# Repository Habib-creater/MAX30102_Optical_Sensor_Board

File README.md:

# MAX30102 Optical Sensor Board

<p align="center">
  <strong>MAX30102 • Dual Supply Rails • I²C • 2-Layer PCB • KiCad</strong>
</p>

<p align="center">
  A compact optical sensing board centered on the MAX30102
  integrated pulse-oximetry and heart-rate sensor.
</p>

<p align="center">
  <a href="docs/max30102_schematic.pdf">Schematic</a> •
  <a href="bom/MAX30102_BOM.csv">BOM</a> •
  <a href="manufacturing/gerbers/">Gerbers</a> •
  <a href="hardware/kicad/">KiCad Files</a>
</p>

---

## Overview

The **MAX30102 Optical Sensor Board** is a compact 2-layer PCB designed
around the **MAX30102** sensor.

The board provides the MAX30102 with dedicated supply regulation,
I²C connectivity, interrupt access, and a 5-pin external interface.

The complete hardware design package is included in this repository,
covering the native **KiCad project**, schematic, PCB layout, BOM,
Gerber and drill manufacturing files, pick-and-place data, and board
documentation.

---

## Quick Access

| Resource | Description |
|---|---|
| 📐 [Schematic PDF](docs/max30102_schematic.pdf) | Electrical schematic |
| 📦 [Bill of Materials](bom/MAX30102_BOM.csv) | Component BOM |
| 🏭 [Gerber & Drill Files](manufacturing/gerbers/) | PCB manufacturing data |
| 🔧 [KiCad Project](hardware/kicad/) | Native KiCad design files |
| 🖼️ [Board Images](docs/images/) | 3D renders and PCB views |
| 📍 [Pick-and-Place Data](manufacturing/pick-and-place/) | Component placement files |

---

## Key Features

| Feature | Details |
|---|---|
| **Optical Sensor** | MAX30102 |
| **Sensor Function** | Pulse oximetry and heart-rate sensing |
| **Digital Interface** | I²C |
| **Interrupt** | Dedicated INT connection |
| **Input Supply** | +5 V |
| **Logic / Sensor Rail** | +3.3 V |
| **LED Supply Rail** | +1.8 V |
| **3.3 V Regulator** | AP2112K-3.3 |
| **1.8 V Regulator** | TLV70018 |
| **Protection** | SMAJ5.0A TVS diode |
| **External Interface** | 1×5 pin header |
| **PCB** | 2-layer |
| **EDA Software** | KiCad |
| **PCB Thickness** | 1.6 mm |
| **Manufacturing Data** | Gerber + PTH/NPTH drill |
| **Assembly Data** | Pick-and-place CSV |

---

## PCB Preview

### 3D Board Render

### PCB Front Layout

### PCB Back Layout

### 3D Bottom View

---

## Hardware Architecture

The board is organized around the MAX30102 sensor and its associated
power and interface circuitry.

### MAX30102 Sensor

The **MAX30102** integrates optical sensing functionality for
pulse-oximetry and heart-rate applications.

The sensor interface exposes:

- I²C clock — SCL
- I²C data — SDA
- Interrupt — INT
- Sensor supply — +1.8 V
- LED supply — +3.3V V

### Power Architecture

The board contains dedicated regulation stages for the sensor system:

- **+5 V input**
- **AP2112K-3.3** for the +3.3 V rail
- **TLV70018** for the +1.8 V rail
- Input transient protection

### External Interface

A 5-pin header provides the primary external connection to the board.

| Pin | Signal |
|---|---|
| 1 | +3.3 V |
| 2 | GND |
| 3 | +5 V |
| 4 | SCL |
| 5 | SDA |

The interrupt signal is routed to the MAX30102 interface circuitry.

---

## PCB Design

The board is implemented as a **2-layer PCB** using **KiCad**.

### PCB Characteristics

- 2-layer signal routing
- 1.6 mm board thickness
- Compact sensor-oriented layout
- Dedicated regulated supply rails
- I²C interface routing
- MAX30102 sensor placement
- Input transient protection
- External 5-pin interface

---

## Design Files

The native KiCad project is located in:

[**hardware/kicad/**](hardware/kicad/)

### Main Files

| File | Description |
|---|---|
| `max30102_pcb.kicad_pro` | KiCad project |
| `max30102_pcb.kicad_sch` | Schematic source |
| `max30102_pcb.kicad_pcb` | PCB layout |

The exported schematic PDF is available in
[**docs/**](docs/).

---

## Manufacturing Outputs

The manufacturing package is available in:

[**manufacturing/gerbers/**](manufacturing/gerbers/)

The package contains:

- Front copper
- Back copper
- Front solder paste
- Back solder paste
- Front silkscreen
- Back silkscreen
- Front solder mask
- Back solder mask
- Board outline
- PTH drill data
- NPTH drill data
- Gerber job file

---

## Bill of Materials

The component BOM is available in:

[**bom/MAX30102_BOM.csv**](bom/MAX30102_BOM.csv)

The BOM contains the component references, quantities, values,
footprints, and available manufacturer/supplier information associated
with the design.

---

## Pick-and-Place Data

Assembly placement data is available in:

[**manufacturing/pick-and-place/**](manufacturing/pick-and-place/)

The package contains separate top-side and bottom-side component
position CSV files.

---

## Documentation

The repository includes:

- Electrical schematic PDF
- PCB front layout
- PCB back layout
- 3D top render
- 3D bottom render
- Bill of materials
- Manufacturing outputs
- Pick-and-place data
- Native KiCad design files

---

## Project Status

| Item | Status |
|---|---|
| Schematic | ✅ Completed |
| PCB Layout | ✅ Completed |
| PCB Layer Count | ✅ 2-layer |
| KiCad Project | ✅ Included |
| BOM | ✅ Included |
| Gerber Files | ✅ Generated |
| Drill Files | ✅ Generated |
| Pick-and-Place Data | ✅ Included |
| Documentation | ✅ Included |

---

## Repository Structure

```text
.
├── hardware/
│   └── kicad/
│       ├── max30102_pcb.kicad_pro
│       ├── max30102_pcb.kicad_sch
│       └── max30102_pcb.kicad_pcb
│
├── manufacturing/
│   ├── gerbers/
│   │   ├── max30102_pcb-F_Cu.gbr
│   │   ├── max30102_pcb-B_Cu.gbr
│   │   ├── max30102_pcb-F_Silkscreen.gbr
│   │   ├── max30102_pcb-B_Silkscreen.gbr
│   │   ├── max30102_pcb-F_Mask.gbr
│   │   ├── max30102_pcb-B_Mask.gbr
│   │   ├── max30102_pcb-F_Paste.gbr
│   │   ├── max30102_pcb-B_Paste.gbr
│   │   ├── max30102_pcb-Edge_Cuts.gbr
│   │   ├── max30102_pcb-PTH.drl
│   │   ├── max30102_pcb-NPTH.drl
│   │   └── max30102_pcb-job.gbrjob
│   │
│   └── pick-and-place/
│       ├── max30102_pcb-top-pos.csv
│       └── max30102_pcb-bottom-pos.csv
│
├── bom/
│   └── MAX30102_BOM.csv
│
├── docs/
│   ├── images/
│   │   ├── 3D_TOP.png
│   │   ├── 3D_BOTTOM.png
│   │   ├── Layout_front.png
│   │   └── Layout_back.png
│   │
│   └── max30102_schematic.pdf
│
├── .gitignore
├── CONTRIBUTING.md
├── LICENSE
└── README.md
```

---

## License

The hardware design files in this repository are licensed under the
**CERN Open Hardware Licence Version 2 - Strongly Reciprocal
(CERN-OHL-S-2.0)**.

The licence permits use, modification, distribution, and manufacture
under the terms of the CERN-OHL-S-2.0 licence, with the corresponding
source-sharing requirements for covered hardware.

**Copyright © 2026 Habib Ur Rehman**

See [`LICENSE`](LICENSE) for the licence identifier and official
licence reference.

---

## Author

### Habib Ur Rehman

**Electronics Engineering**  
**University of Engineering and Technology Peshawar (Abbottabad Campus)**

### Connect

- **GitHub:** [Habib-creater](https://github.com/Habib-creater)
- **LinkedIn:** [Habib Ur Rehman](https://www.linkedin.com/in/habib-ur-rehman-8321182b4/)

---

<p align="center">
  <strong>MAX30102 Optical Sensor Board</strong><br>
  Compact Open Hardware Sensor Platform
</p>

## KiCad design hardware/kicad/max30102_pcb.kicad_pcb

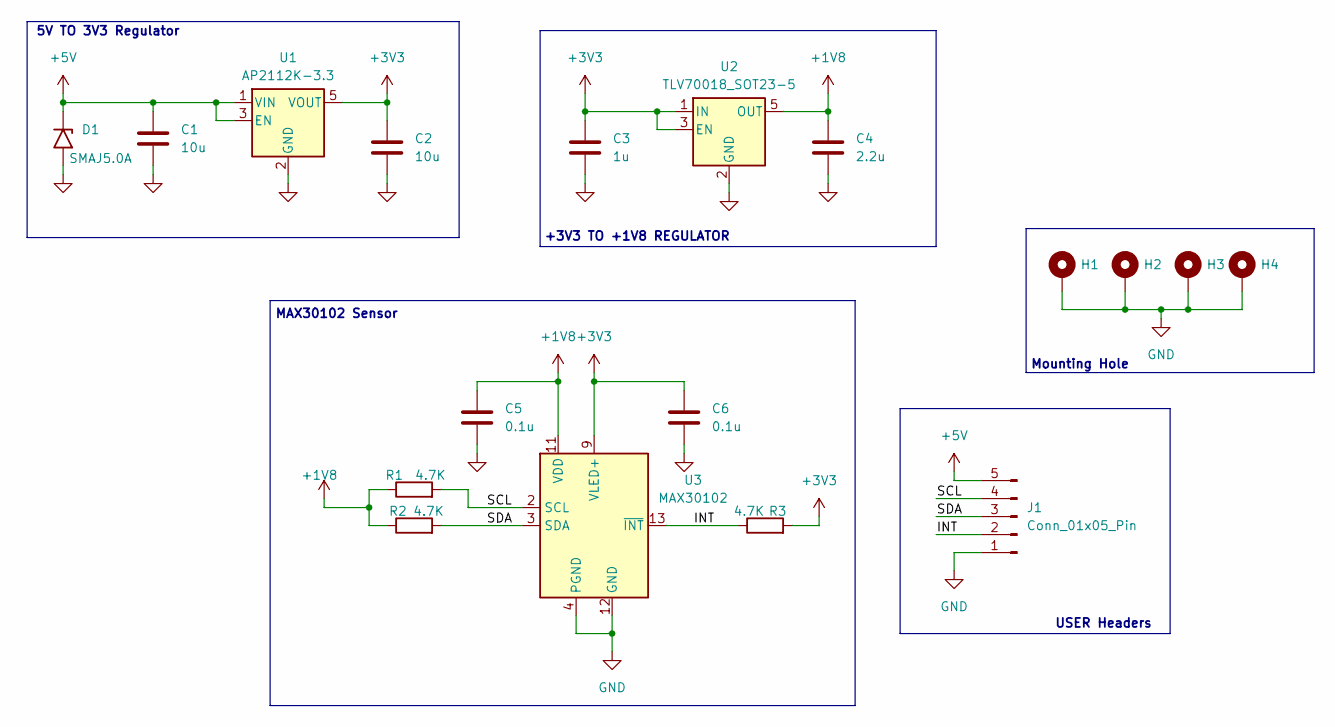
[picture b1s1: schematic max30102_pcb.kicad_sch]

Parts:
C1, C2: 10u; C_0603_1608Metric
C3: 1u; C_0603_1608Metric
C4: 2.2u; C_0603_1608Metric
C5, C6: 0.1u; C_0603_1608Metric
D1: SMAJ5.0A; D_0603_1608Metric_Pad1.05x0.95mm_HandSolder
H1, H2, H3, H4: MountingHole_Pad; MountingHole_2.2mm_M2_Pad_Via
J1: Conn_01x05_Pin; PinHeader_1x05_P2.54mm_Vertical
R1, R2, R3: 4.7K; R_0603_1608Metric_Pad0.98x0.95mm_HandSolder
U1: AP2112K-3.3; SOT-23-5
U2: TLV70018_SOT23-5; SOT-23-5
U3: MAX30102; Maxim_OLGA-14_3.3x5.6mm_P0.8mm

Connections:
+1V8: C4.1, C5.1, R1.1, R2.1, U2.5 (OUT), U3.11 (VDD)
+3V3: C2.1, C3.1, C6.1, R3.2, U1.5 (VOUT), U2.1 (IN), U2.3 (EN), U3.9 (VLED+), U3.10 (VLED+)
+5V: C1.1, D1.1 (A1), J1.5, U1.1 (VIN), U1.3 (EN)
/INT: J1.2, R3.1, U3.13 (~INT)
/SCL: J1.4, R1.2, U3.2 (SCL)
/SDA: J1.3, R2.2, U3.3 (SDA)
GND: C1.2, C2.2, C3.2, C4.2, C5.2, C6.2, D1.2 (A2), H1.1, H2.1, H3.1, H4.1, J1.1, U1.2 (GND), U2.2 (GND), U3.4 (PGND), U3.12 (GND)

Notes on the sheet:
5V TO 3V3 Regulator
Mounting Hole
MAX30102 Sensor
USER Headers
+3V3 TO +1V8 REGULATOR

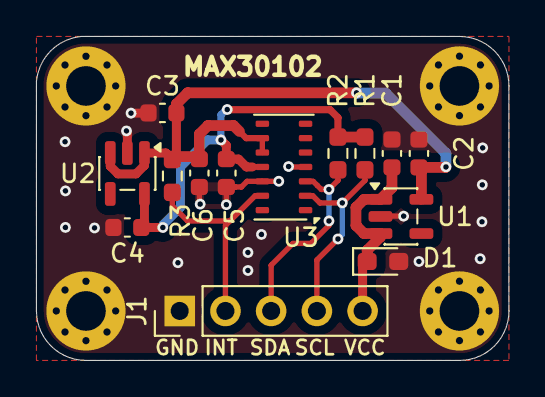
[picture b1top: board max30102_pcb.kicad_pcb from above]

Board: 2 copper layers, 26.2 x 18.0 mm, 18 parts (0 on the bottom side), 7 nets.

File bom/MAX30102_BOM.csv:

Reference,Qty,Value,DNP,Exclude from BOM,Footprint,Datasheet,Manufacturer,Manufacturer part no,Supplier,Supplier Part no,supplier link
"C1,C2",2,10u,,,Capacitor_SMD:C_0603_1608Metric,~,,,,,
C3,1,1u,,,Capacitor_SMD:C_0603_1608Metric,~,,,,,
C4,1,2.2u,,,Capacitor_SMD:C_0603_1608Metric,~,,,,,
"C5,C6",2,0.1u,,,Capacitor_SMD:C_0603_1608Metric,~,,,,,
D1,1,SMAJ5.0A,,,Diode_SMD:D_0603_1608Metric_Pad1.05x0.95mm_HandSolder,https://www.littelfuse.com/media?resourcetype=datasheets&ite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,,,,,
"H1,H2,H3,H4",4,MountingHole_Pad,,Excluded from BOM,MountingHole:MountingHole_2.2mm_M2_Pad_Via,~,,,,,
J1,1,Conn_01x05_Pin,,,Connector_PinHeader_2.54mm:PinHeader_1x05_P2.54mm_Vertical,~,,,,,
"R1,R2,R3",3,4.7K,,,Resistor_SMD:R_0603_1608Metric_Pad0.98x0.95mm_HandSolder,~,,,,,
U1,1,AP2112K-3.3,,,Package_TO_SOT_SMD:SOT-23-5,https://www.diodes.com/assets/Datasheets/AP2112.pdf,,,,,
U2,1,TLV70018_SOT23-5,,,Package_TO_SOT_SMD:SOT-23-5,http://www.ti.com/lit/ds/symlink/tlv700.pdf,,,,,
U3,1,MAX30102,,,OptoDevice:Maxim_OLGA-14_3.3x5.6mm_P0.8mm,https://datasheets.maximintegrated.com/en/ds/MAX30102.pdf,,,,,
